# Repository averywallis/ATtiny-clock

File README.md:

# ATtiny-clock
 A 7-segment display clock controlled by an ATtiny85

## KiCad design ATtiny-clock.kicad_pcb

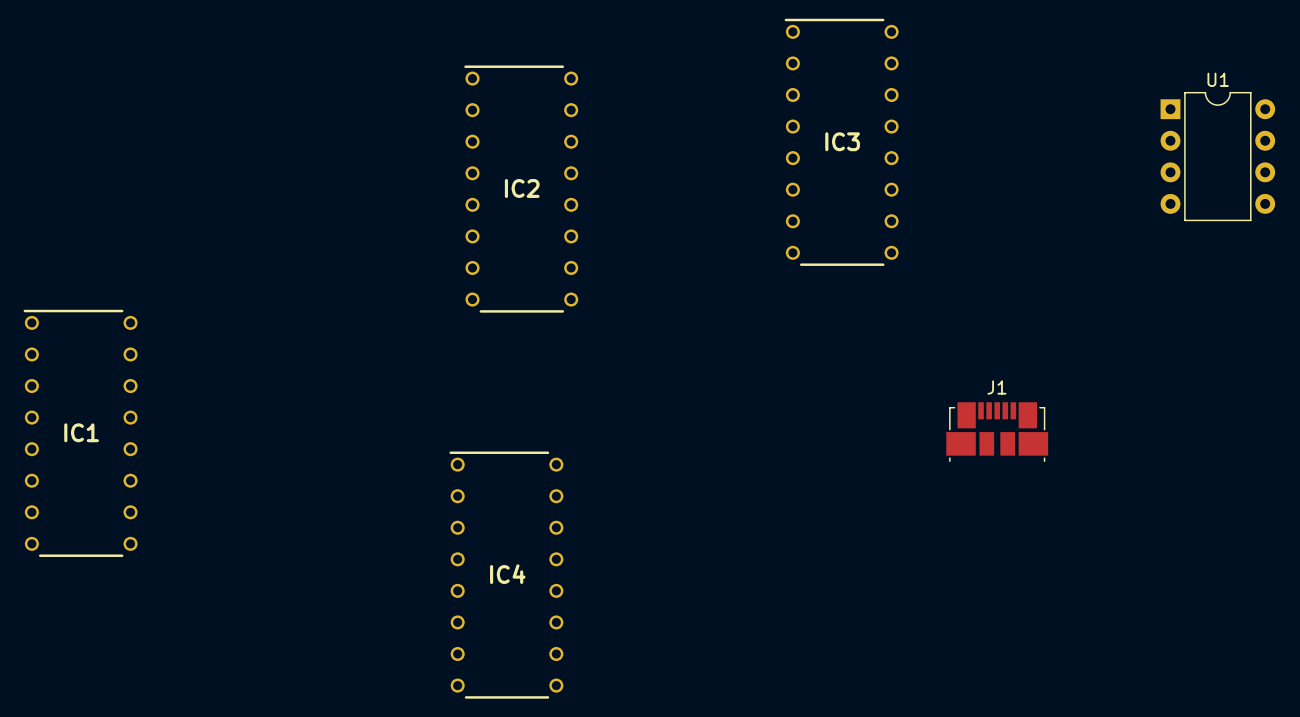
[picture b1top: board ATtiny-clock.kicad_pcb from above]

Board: 2 copper layers, 6 parts (0 on the bottom side), 2 nets, no tracks yet.

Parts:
IC1, IC2, IC3, IC4: SN74HC595N; DIP794W53P254L1930H508Q16N
J1: USB_B_Micro; USB_Micro-B_Molex_47346-0001
U1: ATtiny85-20PU; DIP-8_W7.62mm

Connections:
+5V: IC1.16, IC2.16, IC3.16, IC4.16, J1.1, U1.8
GND: IC1.8, IC2.8, IC3.8, IC4.8, J1.5, U1.4

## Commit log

2022-01-29 Create LICENSE
